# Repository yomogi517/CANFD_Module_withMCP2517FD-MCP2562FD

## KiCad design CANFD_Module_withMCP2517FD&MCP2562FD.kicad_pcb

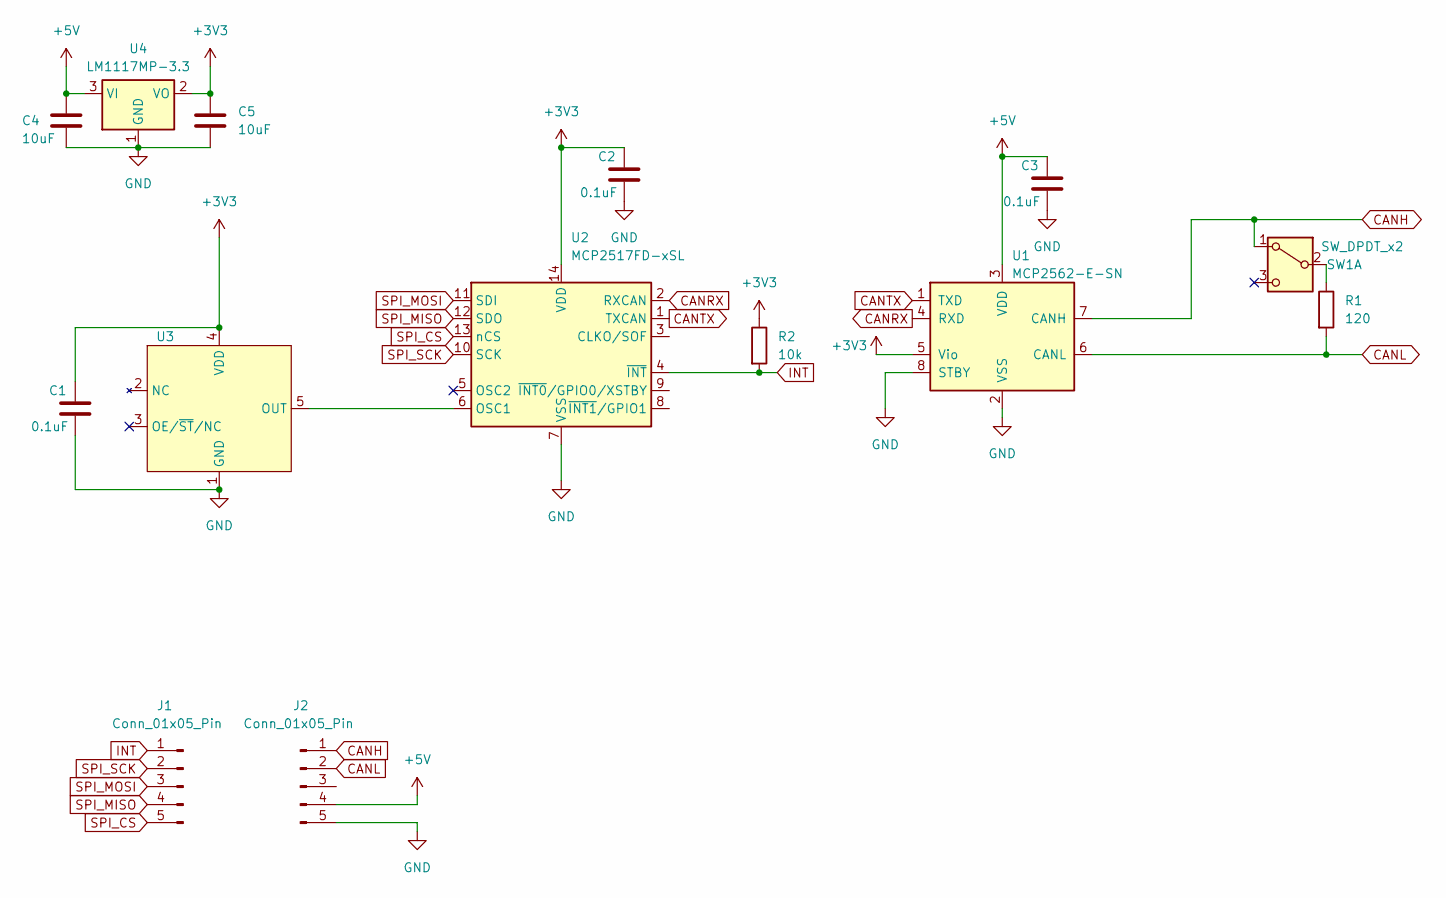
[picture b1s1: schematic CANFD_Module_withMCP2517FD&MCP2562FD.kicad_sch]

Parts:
C1, C2, C3: 0.1uF; C_0603_1608Metric
C4, C5: 10uF; C_0603_1608Metric
J1, J2: Conn_01x05_Pin; PinHeader_1x05_P2.54mm_Vertical
R1: 120; R_0603_1608Metric
R2: 10k; R_0603_1608Metric
SW1: SW_DPDT_x2; SSSS213202
U1: MCP2562-E-SN; SOIC-8_3.9x4.9mm_P1.27mm
U2: MCP2517FD-xSL; SOIC-14_3.9x8.7mm_P1.27mm
U3: SOT-23-5_HandSoldering
U4: LM1117MP-3.3; SOT-223-3_TabPin2

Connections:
+3V3: C1.1, C2.1, C5.1, R2.1, U1.5 (Vio), U2.14 (VDD), U3.4 (VDD), U4.2 (VO)
+5V: C3.1, C4.1, J2.4, U1.3 (VDD), U4.3 (VI)
CANH: J2.1, SW1.1 (A), U1.7 (CANH)
CANL: J2.2, R1.2, U1.6 (CANL)
CANRX: U1.4 (RXD), U2.2 (RXCAN)
CANTX: U1.1 (TXD), U2.1 (TXCAN)
GND: C1.2, C2.2, C3.2, C4.2, C5.2, J2.5, U1.2 (VSS), U1.8 (STBY), U2.7 (VSS), U3.1 (GND), U4.1 (GND)
INT: J1.1, R2.2, U2.4 (~INT)
unnamed: R1.1, SW1.2 (B)
unnamed: U2.6 (OSC1), U3.5 (OUT)
SPI_CS: J1.5, U2.13 (nCS)
SPI_MISO: J1.4, U2.12 (SDO)
SPI_MOSI: J1.3, U2.11 (SDI)
SPI_SCK: J1.2, U2.10 (SCK)

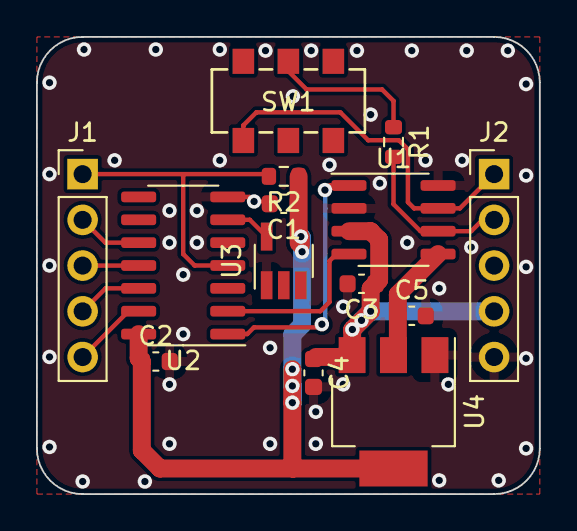
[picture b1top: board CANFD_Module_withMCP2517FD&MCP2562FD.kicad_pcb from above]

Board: 2 copper layers, 27.9 x 25.4 mm, 14 parts (0 on the bottom side), 14 nets.

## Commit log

2024-05-16 add via
